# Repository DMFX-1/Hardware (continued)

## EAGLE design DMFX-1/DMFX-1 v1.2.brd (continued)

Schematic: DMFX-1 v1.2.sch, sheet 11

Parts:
C170, C184, C188: 10u; C0805K; MPN GRM21BR71A106KA73L
C171: 22p; 0402-CAP; MPN GRM1555C2A220JA01D
C172: 8.2n; 0402-CAP; MPN GRM155R71H822KA88D
C173, C177: 1u; 0402-CAP; MPN GRM155R70J105KA12D
C174, C181: 100p; 0402-CAP; MPN GRM1555C1H101FA01J
C175: 33n; 0402-CAP; MPN GRM155R71E333KA88J
C176: 220n; 0402-CAP; MPN GRM155R71C224KA12D
C178: 47p; 0402-CAP; MPN GRM1555C1H470FA01D
C179, C180: 100u; PANASONIC_D; MPN AVE107M25X16T-F
C182: 2.2u; 0402-CAP; MPN GRM155R60J225ME15D
C183: 22u; C1206K; MPN GRM31CR71A226KE15L
C185, C204, C220, C221, C222: 0.1u; C0402K; MPN GRM155R71C104JA88D
C186: 47n; 0402-CAP; MPN GRM155R71H473KE14D
C187: 2.2n; 0402-CAP; MPN GRM155R71H222JA01J
CF1: NFM3DPC223R1H3L; NFM3DC; MPN NFM3DPC223R1H3L
D6: BAT54; SOT23; MPN BAT54LT1G
D8: BAT54S; SOT23; MPN BAT54SLT1G
D9: S1G-13-F; SMADIODE; MPN S1G-13-F
FB12: BLM31PG121SN1L; R1206; MPN BLM31PG121SN1L
IC2: SN74HC4066D; SO14; MPN SN74HC4066DR
J3: STEREOSW3C; NEUTRIK-NMJ6HCD2; MPN NMJ6HCD2
J8: DCJ0202; MPN PJ-202A
JP1: BAT; 1X02; MPN 929834-01-02-RK
Q1, Q2, Q4, Q8, Q9, Q10: MUN2214T1; SC59-BEC; MPN MUN2214T1G
Q3: MMBF4393; SOT23; MPN MMBF4393
R65: 0; 0402-RES; MPN ERJ-2GE0R00X
R144, R145, R149, R157, R169, R170, R174: 10k; 0402-RES; MPN ERJ-2RKF1002X
R146, R147, R168, R198, R199, R200, R201, R202, R203, R204: 100k; 0402-RES; MPN ERJ-2RKF1003X
R148, R150: 2.2k; 0402-RES; MPN ERJ-2RKF2201X
R151: 10k; 0402-RES; MPN ERJ-2RKF3302X
R152: 56k; 0402-RES; MPN ERJ-2RKF1803X
R153: 22k; 0402-RES; MPN ERJ-2RKF5602X
R154, R155, R161, R162: 4.7k; 0402-RES; MPN ERJ-2RKF4701X
R156, R171: 1M; 0402-RES; MPN ERJ-2RKF1004X
R158, R160, R163: 1k; 0402-RES; MPN ERJ-2RKF1001X
R159, R173: 47k; 0402-RES; MPN ERJ-2RKF4702X
R164, R165: 180k; 0402-RES; MPN ERJ-2RKF1803X
R166, R175: 470; 0402-RES; MPN ERJ-2RKF4700X
R167: 560; 0402-RES; MPN ERJ-2RKF5600X
R172: 18k; 0402-RES; MPN ERJ-2RKF1802X
R197: 470; 0402-RES; MPN ERJ-2GE0R00X
SW2: OS102011MA1Q; MPN OS102011MA1QN1
U13: 741G3157DBVR; DBV_R-PDSO-G6; MPN SN74LVC1G3157DBVR
U19, U20, U21: LME49721; SO08; MPN LME49721MAX/NOPB

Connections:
AIC_LINE2L: R175.2; also elsewhere on the board
AIC_LINE2R: R197.2; also elsewhere on the board
BAT+: J8.2, JP1.2
BAT-: J3.R, J3.RN, J8.1, JP1.1
CLEAN: Q10.B; also elsewhere on the board
CLEAN_C: C188.1, R172.2, U20.7 (OUT); also elsewhere on the board
CLEAN_S: C188.2, R65.2, R197.1, R199.1, U13.3 (A)
DCIN: CF1.1, J8.3
DGND: C185.2, C204.2, C220.2, C221.2, C222.2, IC2.7 (VSS), Q2.E, Q4.E, Q8.E, Q9.E, Q10.E, U13.2 (GND); also elsewhere on the board
DIST: C184.2, R200.1, U13.1 (B)
DISTOCT: C183.1; also elsewhere on the board
DIST_OUT: C178.2, IC2.10 (B), R159.2, U21.1 (OUT); also elsewhere on the board
GND-A: C173.2, C177.2, C179.-, C180.-, C182.2, CF1.2@1 (2), D9.A, J3.S, J3.SN, J3.TN, Q1.E, R65.1, R147.1, R156.1, R167.1, R170.1, U19.4 (V-), U20.4 (V-), U21.4 (V-); also elsewhere on the board
LINEIN: C170.1, FB12.2, R169.1
unnamed: C170.2, R144.1
unnamed: C171.1, R144.2, R148.1, R149.1, U19.2 (-IN)
unnamed: R145.2, U19.3 (+IN)
unnamed: C186.1, R169.2
unnamed: C172.1, R148.2
unnamed: C171.2, C172.2, R149.2, U19.1 (OUT), U19.5 (+IN)
unnamed: C173.1, R150.1
unnamed: C174.1, R150.2, R151.1, U19.6 (-IN)
unnamed: C174.2, C175.1, IC2.2 (B), R153.2, R154.1, U19.7 (OUT)
unnamed: IC2.1 (A), IC2.3 (B), R152.2, R153.1
unnamed: IC2.4 (A), R151.2, R152.1
unnamed: C176.1, R154.2, R155.1
unnamed: C175.2, R155.2, U21.3 (+IN)
unnamed: C176.2, Q1.C, R156.2
unnamed: C177.1, IC2.8 (A), R157.1
unnamed: C178.1, C181.1, R158.1, R159.1, R160.1, R161.2, U21.2 (-IN)
unnamed: R163.2, R165.2, U21.5 (+IN)
unnamed: C182.1, R165.1
unnamed: IC2.9 (B), R157.2, R161.1
unnamed: C181.2, D6.3 (C), D8.1 (A1), IC2.11 (A)
unnamed: R162.2, R164.1, U21.6 (-IN)
unnamed: C183.2, R166.1
unnamed: C184.1, R166.2, R167.2
unnamed: FB12.1, J3.T
unnamed: IC2.12 (C), Q2.C, R168.1
unnamed: C180.+, R146.1, R147.2, U20.3 (+IN)
unnamed: C186.2, Q3.3 (G), R171.2
unnamed: IC2.5 (C), Q9.C, R203.1
unnamed: C187.2, R174.1
unnamed: R172.1, R173.2, R174.2, U20.6 (-IN)
unnamed: C187.1, Q3.2 (S), R170.2, R173.1
unnamed: CF1.3, SW2.2
unnamed: IC2.13 (C), Q8.C, R202.1
unnamed: R175.1, R198.1, U13.4 (X)
unnamed: IC2.6 (C), Q2.B, Q4.C, R201.1
unnamed: Q10.C, R204.1, U13.6 (!A!/B)
OCT1: D6.1 (A), R160.2, R162.1
OCT2: D8.2 (C2), R158.2, R163.1
OCT_OUT: R164.2, U21.7 (OUT); also elsewhere on the board
OD_DRV0: Q9.B; also elsewhere on the board
OD_DRV1: Q8.B; also elsewhere on the board
OD_MODE0: Q1.B; also elsewhere on the board
OD_MODE1: Q4.B; also elsewhere on the board
V1.65: R145.1, R171.1, R198.2, R199.2, R200.2, U20.1 (OUT), U20.2 (-IN), U20.5 (+IN); also elsewhere on the board
V3.3A: C179.+, C185.1, C204.1, C220.1, C221.1, C222.1, D9.C, IC2.14 (VDD), Q3.1 (D), R146.2, R168.2, R201.2, R202.2, R203.2, R204.2, U13.5 (VCC), U19.8 (V+), U20.8 (V+), U21.8 (V+); also elsewhere on the board
V3.3AA: SW2.1 (S); also elsewhere on the board

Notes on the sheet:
Line In
Distortion (Overdrive, Crunch, Fuzz)
Clean input
+9V Power input
Octave-Up
Rezzonics
Clean Guitar Line-In Input Buffer-Filter Distortion Line-In Input (Overdrive, Crunch, Fuzz, Octave)
U19
U20
U21

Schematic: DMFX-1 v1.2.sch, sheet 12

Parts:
C189, C197, C206: 220p; 0402-CAP; MPN GRM1555C1H221FA01D
C190, C200: 22p; 0402-CAP; MPN GRM1555C2A220JA01D
C191, C195, C198, C203, C210, C211: 10u; C0805K; MPN GRM21BR71A106KA73L
C192, C193, C196, C199, C201: 2.2n; 0402-CAP; MPN GRM155R71H222JA01J
C194, C202: 150p; 0402-CAP; MPN GRM1555C1H151GA01D
C205, C214: 100p; 0402-CAP; MPN GRM1555C1H101FA01J
C207: 10n; 0402-CAP; MPN GRM155R71E103KA01D
C208: 18n; 0402-CAP; MPN GRM155R71H183KA12D
C209, C223, C224: 0.1u; 0402-CAP; MPN GRM155R71C104JA88D
C212: 680p; 0402-CAP; MPN GRM155R72A681KA01D
D7: BAT54S; SOT23; MPN BAT54SLT1G
FB13, FB14: BLM31PG121SN1L; R1206; MPN BLM31PG121SN1L
J9, J10: MONOSW3C; NEUTRIK-NMJ4HCD2; MPN NMJ4HCD2
LSP3: LSP13; MPN *
Q5, Q6, Q7: 2N7002ET1G; SOT23; MPN 2N7002ET1G
R176, R178, R180, R187, R188, R190, R212: 12k; 0402-RES; MPN ERJ-2RKF1202X
R177, R191: 47k; 0402-RES; MPN ERJ-2RKF4702X
R179, R189: 8.2k; 0402-RES; MPN ERJ-2RKF8201X
R181, R186, R192, R210: 10k; 0402-RES; MPN ERJ-2RKF1002X
R182, R193: 330; 0402-RES; MPN ERJ-2RKF3300X
R183, R194: 100k; 0402-RES; MPN ERJ-2RKF1003X
R184, R185, R195, R196: 1k; 0402-RES; MPN ERJ-2RKF1001X
R205: 100; 0402-RES; MPN ERJ-2RKF1000X
R206: 220k; 0402-RES; MPN ERJ-2RKF2203X
R207, R209: 22k; 0402-RES; MPN ERJ-2RKF2202X
R208: 680k; 0402-RES; MPN ERJ-2RKF6803X
R211: 15k; 0402-RES; MPN ERJ-2RKF1502X
R213, R214: 2k; 0402-RES; MPN ERJ-2RKF2001X
R215, R216: 1.3k; 0402-RES; MPN ERJ-2RKF1301X
U22, U23: LME49721; SO08; MPN LME49721MAX/NOPB
U24: LMV358; SO08; MPN LMV358IDR

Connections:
CLEAN_C: C207.1; also elsewhere on the board
DGND: C205.2, C209.2, C210.2, C212.2, C214.2, R209.1, R212.1, R215.1, R216.1, U24.4 (GND); also elsewhere on the board
GND-A: C192.1, C196.2, C199.1, C223.2, C224.2, J9.S, J10.S, LSP3.MP, Q5.2 (S), R182.1, R183.1, R193.1, R194.1, U22.4 (V-), U23.4 (V-); also elsewhere on the board
LINEOUT_L: C191.1; also elsewhere on the board
LINEOUT_R: C198.1; also elsewhere on the board
MUTE: R186.1; also elsewhere on the board
unnamed: C206.1, D7.1 (A1), D7.2 (C2), R205.2, R208.1, U24.2 (-IN1)
unnamed: C190.1, R177.1, R179.2, R181.1, U22.6 (-IN)
unnamed: C192.2, R176.1, R178.1, R180.2
unnamed: C190.2, C193.2, C194.1, C195.1, R177.2, U22.7 (OUT)
unnamed: C189.2, R176.2, R179.1, U22.1 (OUT)
unnamed: C193.1, R181.2
unnamed: C191.2, R180.1
unnamed: C189.1, R178.2, U22.2 (-IN)
unnamed: C194.2, R182.2
unnamed: Q5.3 (D), Q6.3 (D), Q7.3 (D)
unnamed: C195.2, R183.2, R184.1
unnamed: Q6.2 (S), R184.2, R185.1
unnamed: FB13.1, J9.T
unnamed: C196.1, Q5.1 (G), Q6.1 (G), Q7.1 (G), R186.2
unnamed: FB13.2, R185.2
unnamed: C199.2, R187.1, R188.1, R190.2
unnamed: C197.2, R187.2, R189.1, U23.1 (OUT)
unnamed: C198.2, R190.1
unnamed: C197.1, R188.2, U23.2 (-IN)
unnamed: C200.1, R189.2, R191.1, R192.1, U23.6 (-IN)
unnamed: C200.2, C201.2, C202.1, C203.1, R191.2, U23.7 (OUT)
unnamed: C201.1, R192.2
unnamed: C202.2, R193.2
unnamed: C203.2, R194.2, R195.1
unnamed: Q7.2 (S), R195.2, R196.1
unnamed: FB14.1, J10.T
unnamed: FB14.2, R196.2
unnamed: C206.2, C208.1, R208.2, R213.1, U24.1 (OUT1), U24.6 (-IN2)
unnamed: C210.1, C211.2, R206.1, R207.1, R209.2
unnamed: C207.2, R210.1
unnamed: C205.1, D7.3 (C1A2), R206.2, R210.2, U24.3 (+IN1)
unnamed: C211.1, R205.1
unnamed: C208.2, C212.1, R211.1, R212.2, U24.5 (+IN2)
unnamed: R214.1, U24.7 (OUT2)
NOISE_SUP: R213.2, R216.2; also elsewhere on the board
TUNER: C214.1, R214.2, R215.2; also elsewhere on the board
V1.65: U22.3 (+IN), U22.5 (+IN), U23.3 (+IN), U23.5 (+IN); also elsewhere on the board
V3.3A: C209.1, C223.1, C224.1, R207.2, R211.2, U22.8 (V+), U23.8 (V+), U24.8 (+V); also elsewhere on the board

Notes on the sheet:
Line Out L
Line Out R
Rezzonics
Output Buffer/Filter Line-Out Mute
Tuner - Noise Supressor level
U24
U23
U22

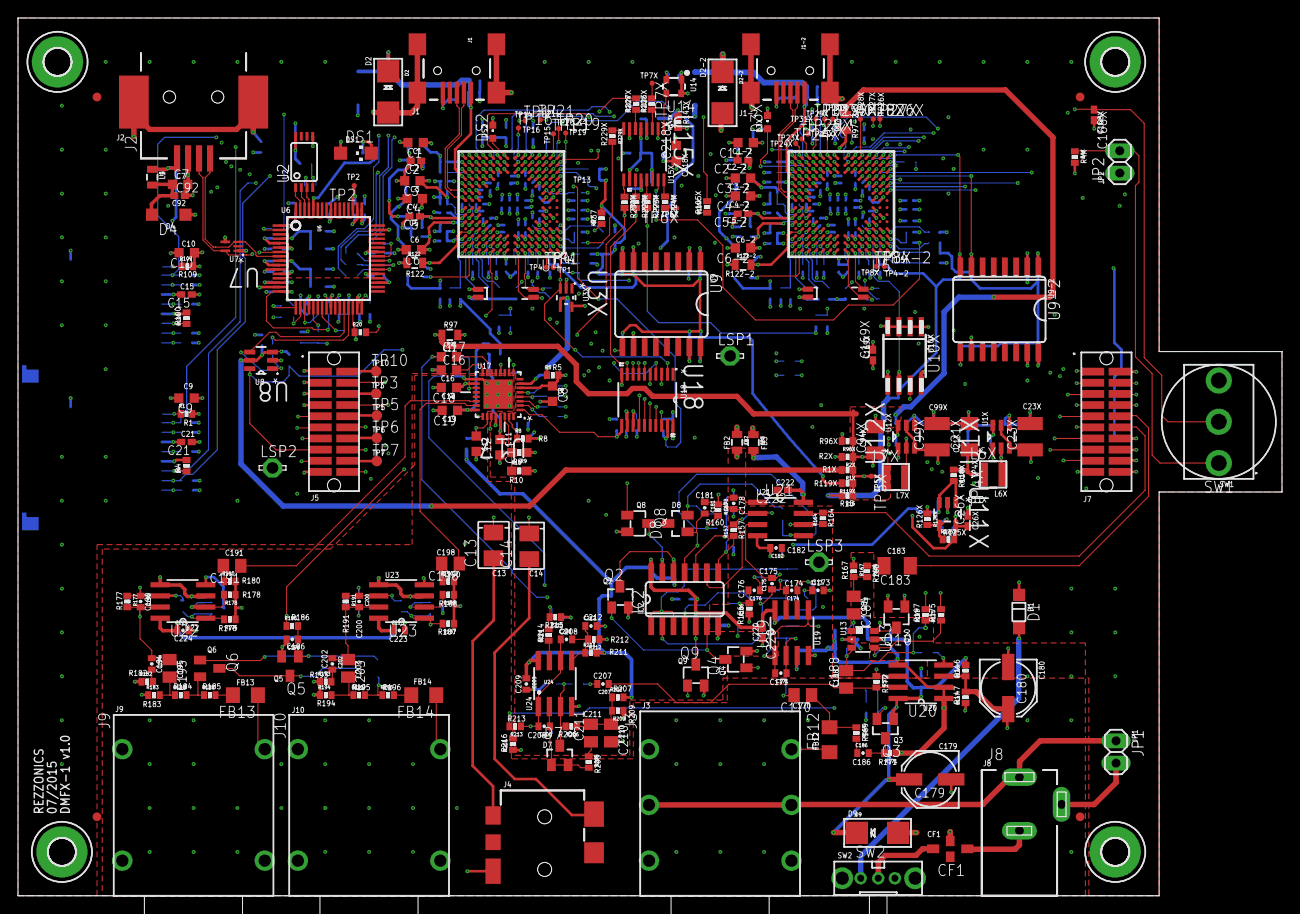
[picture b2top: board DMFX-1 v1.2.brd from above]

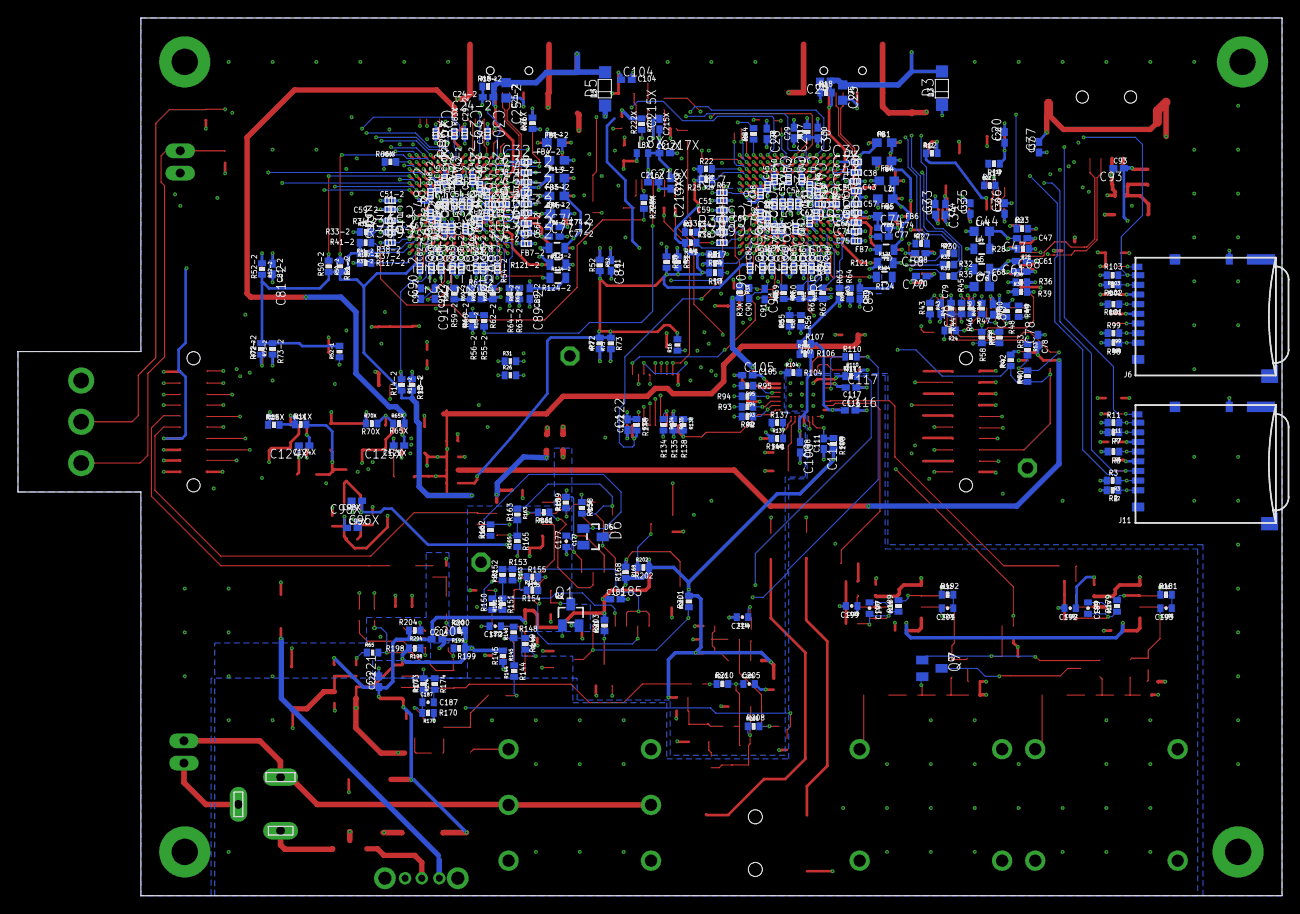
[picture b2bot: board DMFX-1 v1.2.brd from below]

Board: 6 copper layers, 144.0 x 100.0 mm, 570 parts (320 on the bottom side), 361 nets.

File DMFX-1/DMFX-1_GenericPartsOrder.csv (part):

Part Number,Mfg Name,VID,Vendor Part Num,Description,Customer Ref,Part Value,Qty-1,Qty-5,Qty-25,Part References,Value
ERJ-2GE0R00X,Panasonic,DK,P0.0JCT-ND,RES SMD 0.0 OHM JUMPER 1/10W 0402,res074,0,6,30,150,"R38, R38-2, R54, R54-2, R67, R83X",0
ERJ-2GE0R00X,Panasonic,DK,P0.0JCT-ND,RES SMD 0.0 OHM JUMPER 1/10W 0402,res074,0,29,145,725,"R1X, R2X, R5, R8, R15, R23, R27, R30, R32, R35, R55, R55-2, R60, R60-2, R61, R61-2, R64, R64-2, R84, R92, R93, R94, R95, R96X, R105X, R108, R118X, R119X, R197",0
ERJ-2GE0R00X,Panasonic,DK,P0.0JCT-ND,RES SMD 0.0 OHM JUMPER 1/10W 0402,res074,0,1,5,25,R97,0
ERJ-6GEY0R00V,Panasonic,DK,P0.0ACT-ND,RES SMD 0.0 OHM JUMPER 1/8W 0805,res104,0,5,25,125,"R97-2, R122, R122-2, R124, R124-2",0
GRM155R71C104JA88D,Murata,DK,490-6327-1-ND,CAP CER 0.1UF 16V 5% X7R 0402,capcer042,100n,41,205,1025,"C15, C20, C21, C24, C24-2, C28, C29, C30, C34, C35, C36, C47, C61, C68, C70, C77, C77-2, C78, C79, C80, C81, C81-2, C92, C98X, C105, C108, C111, C116, C117, C122, C124X, C125X, C169X, C185, C204, C213X, C215X, C216X, C220, C221, C222",0.1u
GRM155R71C104JA88D,Murata,DK,490-6327-1-ND,CAP CER 0.1UF 16V 5% X7R 0402,capcer042,100n,47,235,1175,"C28-2, C29-2, C30-2, C32, C32-2, C40, C40-2, C45, C45-2, C46, C46-2, C48, C48-2, C49, C49-2, C57, C57-2, C59, C59-2, C60, C60-2, C62, C62-2, C63, C63-2, C65, C65-2, C67, C67-2, C69, C69-2, C71, C71-2, C72, C72-2, C75, C75-2, C82, C82-2, C84, C84-2, C85, C85-2, C87, C87-2, C88, C88-2",0.1u
GRM155R71C104JA88D,Murata,DK,490-6327-1-ND,CAP CER 0.1UF 16V 5% X7R 0402,capcer042,100n,3,15,75,"C209, C223, C224",0.1u
GRM188R71C474KA88D,Murata,DK,490-3295-1-ND,CAP CER 0.47UF 16V 10% X7R 0603,capcer046,470n,2,10,50,"C16, C17",0.47u
ERJ-2RKF1301X,Panasonic,DK,P1.30KLCT-ND,RES SMD 1.3K OHM 1% 1/10W 0402,res075,1.3k,2,10,50,"R215, R216",1.3k
ERJ-2RKF1004X,Panasonic,DK,P1.00MLCT-ND,RES SMD 1M OHM 1% 1/10W 0402,res076,1M,2,10,50,"R156, R171",1M
ERJ-2RKF1001X,Panasonic,DK,P1.00KLCT-ND,RES SMD 1K OHM 1% 1/10W 0402,res077,1k,9,45,225,"R110, R111, R158, R160, R163, R184, R185, R195, R196",1k
GRM155R71H102JA01J,Murata,DK,490-6349-1-ND,CAP CER 1000PF 50V 5% X7R 0402,capcer043,1n,2,10,50,"C74, C74-2",1n
GRM155R71H102JA01J,Murata,DK,490-6349-1-ND,CAP CER 1000PF 50V 5% X7R 0402,capcer043,1n,6,30,150,"C50, C50-2, C56, C56-2, C66, C66-2",1n
GRM155R70J105KA12D,Murata,DK,490-10024-1-ND,CAP CER 1UF 6.3V 10% 0402,capcer047,1u,6,30,150,"C2, C2-2, C5, C5-2, C26X, C217X",1u
GRM155R70J105KA12D,Murata,DK,490-10024-1-ND,CAP CER 1UF 6.3V 10% 0402,capcer047,1u,14,70,350,"C42, C42-2, C52, C52-2, C53, C53-2, C54, C54-2, C64, C64-2, C83, C83-2, C86, C86-2",1u
GRM155R70J105KA12D,Murata,DK,490-10024-1-ND,CAP CER 1UF 6.3V 10% 0402,capcer047,1u,2,10,50,"C173, C177",1u
ERJ-2RKF2201X,Panasonic,DK,P2.20KLCT-ND,RES SMD 2.2K OHM 1% 1/10W 0402,res078,2.2k,3,15,75,"R21, R148, R150",2.2k
GRM155R71H222JA01J,Murata,DK,490-6359-1-ND,CAP CER 2200PF 50V 5% X7R 0402,capcer044,2.2n,6,30,150,"C187, C192, C193, C196, C199, C201",2.2n
GRM155R60J225ME15D,Murata,DK,490-4519-1-ND,CAP CER 2.2UF 6.3V 20% X5R 0402,capcer045,2.2u,1,5,25,C182,2.2u
SRN3015-2R2M,Bourns,DK,SRN3015-2R2MCT-ND,FIXED IND 2.2UH 1.8A 72 MOHM SMD,ind005,2.2u,1,5,25,L6X,2.2u
2N7002ET1G,ON Semiconductor,DK,2N7002ET1GOSCT-ND,MOSFET N-CH 60V 260MA SOT-23,mos003,2N7002,3,15,75,"Q5, Q6, Q7",2N7002ET1G
ERJ-2RKF2001X,Panasonic,DK,P2.00KLCT-ND,RES SMD 2K OHM 1% 1/10W 0402,res079,2k,2,10,50,"R213, R214",2k
SRN3015-3R3M,Bourns,DK,SRN3015-3R3MCT-ND,FIXED IND 3.3UH 1.6A 112 MOHM,ind006,3.3u,1,5,25,L7X,3.3u
ERJ-2RKF4701X,Panasonic,DK,P4.70KLCT-ND,RES SMD 4.7K OHM 1% 1/10W 0402,res080,4.7k,7,35,175,"R57, R104, R136, R154, R155, R161, R162",4.7k
ERJ-3EKF4701V,Panasonic,DK,P4.70KHCT-ND,RES SMD 4.7K OHM 1% 1/10W 0603,res027,4.7k,1,5,25,R10,4.7k
GRM188R60J475KE19D,Murata,DK,490-3297-1-ND,CAP CER 4.7UF 6.3V 10% X5R 0603,capcer048,4.7u,2,10,50,"C44, C76",4.7u
1SMA5920BT3G,ON Semiconductor,DK,1SMA5920BT3GOSCT-ND,DIODE ZENER 6.2V 1.5W SMA,diodez004,1SMA5920,2,10,50,"D2, D2-2",6.2V
ERJ-2RKF8201X,Panasonic,DK,P8.20KLCT-ND,RES SMD 8.2K OHM 1% 1/10W 0402,res081,8.2k,2,10,50,"R179, R189",8.2k
GRM155R71H822KA88D,Murata,DK,490-6365-1-ND,CAP CER 8200PF 50V 10% X7R 0402,capcer049,8.2n,1,5,25,C172,8.2n
ERJ-2RKF10R0X,Panasonic,DK,P10.0LCT-ND,RES SMD 10 OHM 1% 1/10W 0402,res082,10,8,40,200,"R223X, R224X, R225X, R226X, R227X, R228X, R229X, R230X",10
ERJ-2RKF1002X,Panasonic,DK,P10.0KLCT-ND,RES SMD 10K OHM 1% 1/10W 0402,res083,10k,2,10,50,"R29, R29-2",10k
ERJ-2RKF1002X,Panasonic,DK,P10.0KLCT-ND,RES SMD 10K OHM 1% 1/10W 0402,res083,10k,57,285,1425,"R1, R2, R3, R3X, R4, R4X, R7, R11, R13, R13-2, R14, R14-2, R15X, R19, R22, R25, R33, R33-2, R36, R42, R43, R44, R50, R50-2, R51, R51-2, R52, R52-2, R59, R59-2, R70X, R98, R99, R100, R102, R103, R109, R117, R117-2, R134, R135, R138, R143X, R144, R145, R149, R157, R169, R170, R174, R181, R183, R186, R192, R194, R210, R222X",10k
GRM155R71E103KA01D,Murata,DK,490-1312-1-ND,CAP CER 10000PF 25V 10% X7R 0402,capcer050,10n,7,35,175,"C33, C37, C58, C89, C89-2, C93, C104",10n
GRM155R71E103KA01D,Murata,DK,490-1312-1-ND,CAP CER 10000PF 25V 10% X7R 0402,capcer050,10n,12,60,300,"C38, C38-2, C41, C41-2, C43, C43-2, C51, C51-2, C55, C55-2, C73, C73-2",10n
GRM155R71E103KA01D,Murata,DK,490-1312-1-ND,CAP CER 10000PF 25V 10% X7R 0402,capcer050,10n,1,5,25,C207,10n
GRM1555C1H100FA01D,Murata,DK,490-6186-1-ND,CAP CER 10PF 50V 1% NP0 0402,capcer051,10p,4,20,100,"C90, C90-2, C91, C91-2",10p
GRM21BR71A106KA73L,Murata,DK,490-10516-1-ND,CAP CER 10UF 10V 10% X7R 0805,capcer053,10u,9,45,225,"C170, C184, C188, C191, C195, C198, C203, C210, C211",10u
GRM188R61C106MA73D,Murata,DK,490-7201-1-ND,CAP CER 10UF 16V 20% X5R 0603,capcer052,10u,19,95,475,"C1, C1-2, C3, C3-2, C4, C4-2, C6, C6-2, C7, C8, C9, C10, C11, C12, C18, C19, C25, C25-2, C218X",10u
ERJ-2RKF1202X,Panasonic,DK,P12.0KLCT-ND,RES SMD 12K OHM 1% 1/10W 0402,res084,12k,8,40,200,"R28, R176, R178, R180, R187, R188, R190, R212",12k
ERJ-2RKF1372X,Panasonic,DK,P13.7KLCT-ND,RES SMD 13.7K OHM 1% 1/10W 0402,res085,13.7k,1,5,25,R11X,13.7k
ERJ-2RKF1502X,Panasonic,DK,P15.0KLCT-ND,RES SMD 15K OHM 1% 1/10W 0402,res086,15k,1,5,25,R211,15k
ERJ-2RKF1802X,Panasonic,DK,P18.0KLCT-ND,RES SMD 18K OHM 1% 1/10W 0402,res087,18k,1,5,25,R172,18k
GRM155R71H183KA12D,Murata,DK,490-6356-1-ND,CAP CER 0.018UF 50V 10% X7R 0402,capcer054,18n,1,5,25,C208,18n
ERJ-2RKF2052X,Panasonic,DK,P20.5KLCT-ND,RES SMD 20.5K OHM 1% 1/10W 0402,res088,20.5k,1,5,25,R125X,20.5k
ERJ-2RKF2202X,Panasonic,DK,P22.0KLCT-ND,RES SMD 22K OHM 1% 1/10W 0402,res089,22k,2,10,50,"R207, R209",22k
GRM1555C2A220JA01D,Murata,DK,490-7303-1-ND,CAP CER 22PF 100V 5% NP0 0402,capcer055,22p,3,15,75,"C171, C190, C200",22p
GRM31CR71A226KE15L,Murata,DK,490-5309-1-ND,CAP CER 22UF 10V 10% X7R 1206,capcer056,22u,3,15,75,"C21X, C94X, C183",22u
GRM32ER71E226ME15L,Murata,DK,490-10758-1-ND,CAP CER 22UF 25V 20% X7R 1210,capcer066,22u,2,10,50,"C23X, C99X",22u
AT24C64D-SSHM-T,Atmel,DK,AT24C64D-SSHM-TCT-ND,IC EEPROM 64KBIT 1MHZ 8SOIC,icmem001,24C64,1,5,25,U10X,24C64SM
SSPT7F-12.5PF20-R,Seiko Instruments,DK,728-1064-1-ND,CRYSTAL 32.7680KHZ 12.5PF SMD,xtal001,32.768kHz,2,10,50,"Y1, Y1-2",32.768kHz
ERJ-2RKF33R0X,Panasonic,DK,P33.0LCT-ND,RES SMD 33 OHM 1% 1/10W 0402,res105,33,8,40,200,"R39, R46, R47, R48, R49, R53, R58, R66X",33
ERJ-2RKF3322X,Panasonic,DK,P33.2KLCT-ND,RES SMD 33.2K OHM 1% 1/10W 0402,res090,33.2k,1,5,25,R65X,33.2k
ERJ-2RKF3302X,Panasonic,DK,P33.0KLCT-ND,RES SMD 33K OHM 1% 1/10W 0402,res091,33k,1,5,25,R151,33k
GRM155R71E333KA88J,Murata,DK,490-6345-1-ND,CAP CER 0.033UF 25V 10% X7R 0402,capcer057,33n,1,5,25,C175,33n
ERJ-2RKF4702X,Panasonic,DK,P47.0KLCT-ND,RES SMD 47K OHM 1% 1/10W 0402,res092,47k,4,20,100,"R159, R173, R177, R191",47k
GRM155R71H473KE14D,Murata,DK,490-10702-1-ND,CAP CER 0.047UF 50V 10% X7R 0402,capcer058,47n,1,5,25,C186,47n
GRM1555C1H470FA01D,Murata,DK,490-6241-1-ND,CAP CER 47PF 50V 1% NP0 0402,capcer059,47p,1,5,25,C178,47p
ERJ-2RKF5602X,Panasonic,DK,P56.0KLCT-ND,RES SMD 56K OHM 1% 1/10W 0402,res093,56k,1,5,25,R153,56k
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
